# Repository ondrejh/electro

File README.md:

Electro
=======

Tariff device logging according to IEC 62056-21.

## Description:
The device is based on Raspberry PI, with the optical head connected to it. It reads the tariff values every 15 minutes and saves it into the database file. The device has the web interface displayin the captured data in chart.

## Files:
[tariff.py](https://github.com/ondrejh/electro/blob/master/script/tariff.py): access tariff device and store reading into sqlite database file.

doc: some resouces

hw: optical head documentation

## Instalation:
will be done later

## ToDo:
- calculate time of the high-low tariff switching
- display it
- some more description (schematics, head documentation, photos ...)

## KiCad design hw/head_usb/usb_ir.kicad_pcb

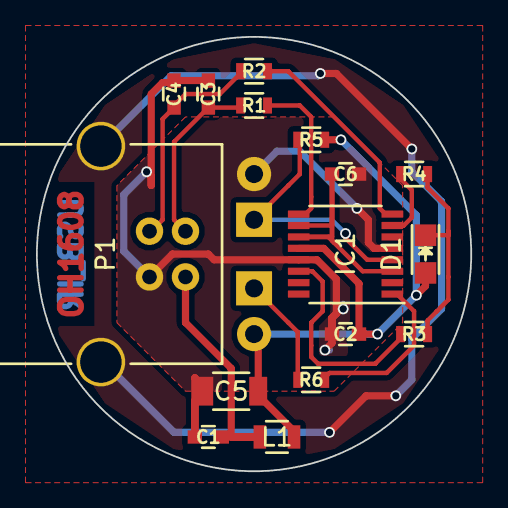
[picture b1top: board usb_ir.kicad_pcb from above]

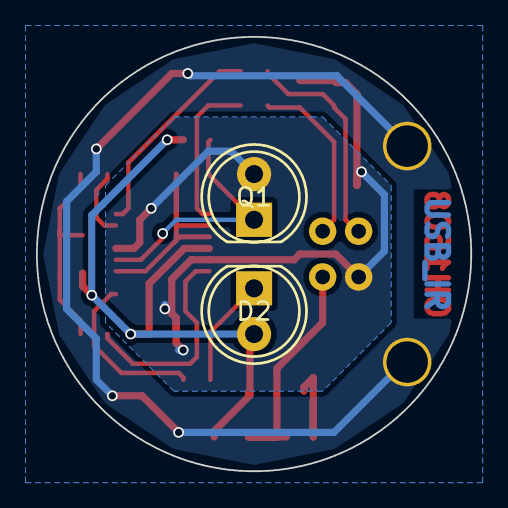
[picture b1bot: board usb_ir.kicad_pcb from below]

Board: 2 copper layers, 24.1 x 24.1 mm, 18 parts (2 on the bottom side), 14 nets.

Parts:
C1: 10n; C_0603
C2, C6: 100n; C_0603
C3, C4: 47p; C_0603
C5: 4u7; C_1206
D1: LED_RD; LED_0805
D2: L-53F3C; LED-5MM
IC1: FT230XS; SSOP-16_3.9x4.9mm_Pitch0.635mm
L1: FERRITE; R_0805
P1: USB_B
Q1: L-53P3C; LED-5MM
R1, R2: 27R; R_0603
R3, R4: 470R; R_0603
R5: 4k7; R_0603
R6: 390R; R_0603

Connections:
/RXD: IC1.4, Q1.1, R5.1
/TXD: IC1.1, R6.2
/~RXLED: IC1.14, R3.2
/~TXLED: IC1.7, R4.2
GND: C1.2, C2.2, C3.2, C4.2, C5.2, C6.2, IC1.5, IC1.13, P1.4, Q1.2
unnamed: C1.1, L1.2, P1.1
unnamed: C3.1, P1.2, R1.2
unnamed: C4.1, P1.3, R2.2
unnamed: C6.1, IC1.3, IC1.10, IC1.11
unnamed: D1.1, R3.1, R4.1
unnamed: D2.1, R6.1
unnamed: IC1.8, R2.1
unnamed: IC1.9, R1.1
VCC: C2.1, C5.1, D1.2, D2.2, IC1.12, L1.1, R5.2

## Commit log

2014-05-17 resources, first readout scrip and data
2014-05-17 optho connector prototype schematic
2014-05-17 optical head documentation
2014-05-17 file description
2014-05-17 some foggy snapshots
2014-05-18 some notes into schematic
2014-05-18 response block join and split functions
2014-05-19 size of data chunk
2014-05-19 some examples of html5 charts
2014-05-25 port power, portname debug
2014-05-26 colours
2014-05-26 db connect
2014-06-11 db test
2014-06-11 second prototype asembly note (text)
2014-06-12 silent data reading (no printout)
2014-06-12 optho head mechanical parts drawing (thanks AA)
2014-06-16 crontab hint
2014-06-17 some more notes
2014-06-17 executable mode
2014-06-17 rpi uart port
2014-06-17 show last entry function
2014-06-17 forgotten str format args
2014-06-17 another db debug
2014-06-17 this wound work
2014-06-17 trying type
2014-06-17 trying type of first entry
2014-06-18 debug of return_last_entry function (and test script)
2014-06-18 test database
2014-06-19 get last entry function / tests
2014-06-19 wattage calculation
2014-06-19 limits in return_data function - need to test all posibilities
2014-06-19 executable
2014-06-19 wrong exec
2014-06-19 dump wattage into file
2014-06-19 first gnuplot test
2014-06-23 new test data
2014-06-24 get day data
2014-06-25 one day plotting gnuplot script file
2014-06-25 day data / all day datafiles
2014-06-25 test renamed to utils
2014-06-25 changed run with file
2014-06-25 copy files to rpi
2014-06-26 configuration and run script
2014-06-26 run with dbconn
2014-06-26 throw away www
2014-06-26 cleanup
2014-06-26 html template
2014-06-27 different dir and debug
2014-07-09 two day plotting (if possible)
2014-07-09 local test configuration
2014-07-09 discart debug output
2014-07-23 log dump
2014-07-23 some debugging
2014-08-11 web interface
2014-08-11 self propelled gnuplot_calls (plus run function)
2014-08-11 funny picture
2014-08-15 log commented out
2014-08-15 gnuplot cron debugged
2014-08-20 chart gallery using lightbox
2014-08-31 checksum=OK added
2015-11-09 php image gallery generator
2015-11-09 negative
2015-12-03 tarif recognition (blind test)
2015-12-03 tarif file output - debug
2016-08-29 nochage
2016-08-29 usb head pcb
2016-08-29 usb head pcb - overview (rendered)
2016-08-29 gerber files
2016-08-29 datasheets
2018-12-14 lame schematic
2019-01-02 new python script (just the folder, lcd test and get_ip function)
2019-01-02 colorfull and useless ...
2019-01-03 lcd backlight and test
2019-01-03 button inputs
2019-01-26 display with several pages
2019-01-26 button edge detector
2019-01-26 clock
2019-01-26 lcd library file renamed
2019-01-26 service file
2019-01-26 copy of electro.py
2019-01-26 tariff device reading routine - copy of old electro.py
2019-01-27 decode functions siplified, run example improved
2019-01-28 db connect (first step)
2019-01-29 storing data with new system, finally
2019-01-29 todo
2019-01-30 db design
2019-02-03 database repair script
2019-02-03 get values from message body
2019-02-10 data read with php
2019-02-10 decode reading
2019-02-10 server export script
2019-02-10 first plotly watage chart .. hurray
2019-02-10 renamed to index
2019-02-10 refactorize
2019-02-10 new -> actual
2019-02-10 3 day watage
2019-02-10 use rsync instead of scp
2019-02-10 yet another castling
2019-02-10 readme update (partial)
2019-02-24 one line only (no zero watages)
2019-02-24 calculate changes
2019-02-24 only one chart
2019-02-24 calculations rounding
2019-02-24 last reading
2019-02-27 whole week, better last reading formating
2019-03-01 date format
